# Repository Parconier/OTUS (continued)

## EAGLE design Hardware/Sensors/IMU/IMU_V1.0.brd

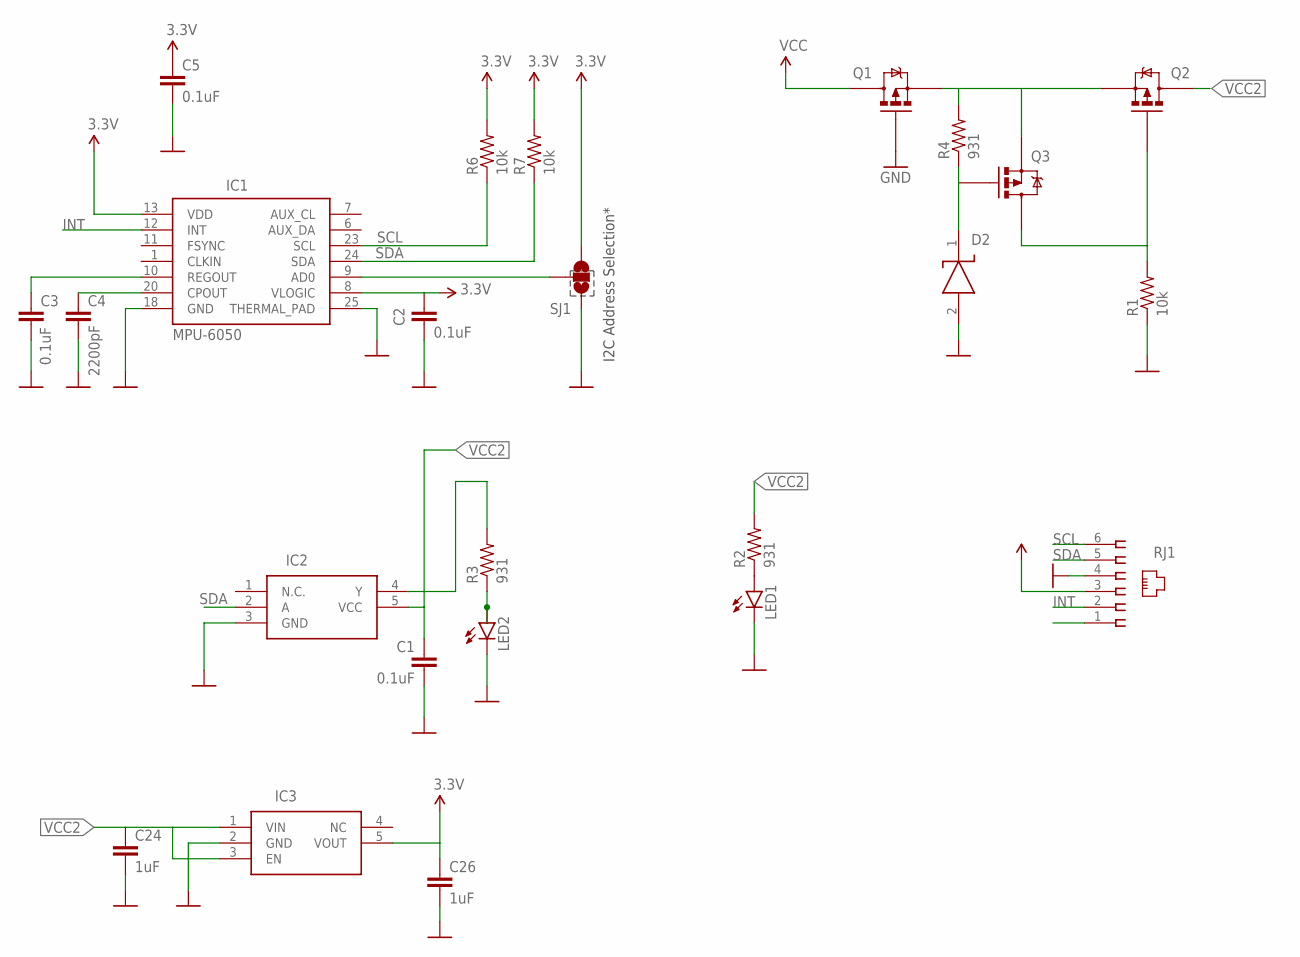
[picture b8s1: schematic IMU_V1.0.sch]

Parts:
C1, C2, C3, C5: 0.1uF; 0402; MPN CC0402KRX5R9BB104
C4: 2200pF; 0402; MPN GRM155R71H222JA01D
C24, C26: 1uF; 0402; MPN CC0402ZRY5V6BB105
D2: BZT52C5V1-7-F; SOD3716X145N; MPN BZT52C5V1-7-F
IC1: MPU-6050; QFN50P400X400X95-25N; MPN MPU-6050
IC2: 74LVC1G14GW-Q100,1; SOT65P212X110-5N; MPN 74AHC1G14GW-Q100,1
IC3: MIC5504-3.3YM5-TR; SOT95P280X145-5N; MPN MIC5504-3.3YM5-TR
LED1: LED0603; LED-0603; MPN LTST-C193KRKT-5A
LED2: LED0603; LED-0603; MPN LB Q39E-L2OO-35-1
Q1: RU1C002ZPTCL; SOTFL65P210X105-3N; MPN RU1C002ZPTCL
Q2, Q3: RU1C002ZPTCL; SOTFL65P210X105-3N; MANUFACTURER_PART_NUMBER RU1C002ZPTCL
R1, R6, R7: 10k; RESC1005X35; MPN RC0402JR-7W10KL
R2, R3, R4: 931; RESC1005X35; MPN RC0402FR-07931RL
RJ1: 615006138421; MPN 615006138421
SJ1: SOLDERJUMPER_2WAYPASTE2&3; SJ_3_PASTE2&3

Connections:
3.3V: C2.1, C5.1, C26.1, IC1.8 (VLOGIC), IC1.13 (VDD), IC3.5 (VOUT), R6.2, R7.2, SJ1.1
GND: C1.2, C2.2, C3.2, C4.2, C5.2, C24.2, C26.2, D2.2 (A), IC1.18 (GND), IC1.25 (THERMAL_PAD), IC2.3 (GND), IC3.2 (GND), LED1.C, LED2.C, Q1.1 (G), R1.1, RJ1.4, SJ1.3
INT: IC1.12 (INT), RJ1.2
unnamed: Q1.2 (S), Q2.2 (S), Q3.2 (S), R4.2
unnamed: Q2.1 (G), Q3.3 (D), R1.2
unnamed: D2.1 (K), Q3.1 (G), R4.1
unnamed: IC2.4 (Y), R3.2
unnamed: LED2.A, R3.1
unnamed: C4.1, IC1.20 (CPOUT)
unnamed: C3.1, IC1.10 (REGOUT)
unnamed: IC1.9 (AD0), SJ1.2
unnamed: LED1.A, R2.1
SCL: IC1.23 (SCL), R6.1, RJ1.6
SDA: IC1.24 (SDA), IC2.2 (A), R7.1, RJ1.5
VCC: Q1.3 (D), RJ1.3
VCC2: C1.1, C24.1, IC2.5 (VCC), IC3.1 (VIN), IC3.3 (EN), Q2.3 (D), R2.2

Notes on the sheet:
I2C Address Selection*

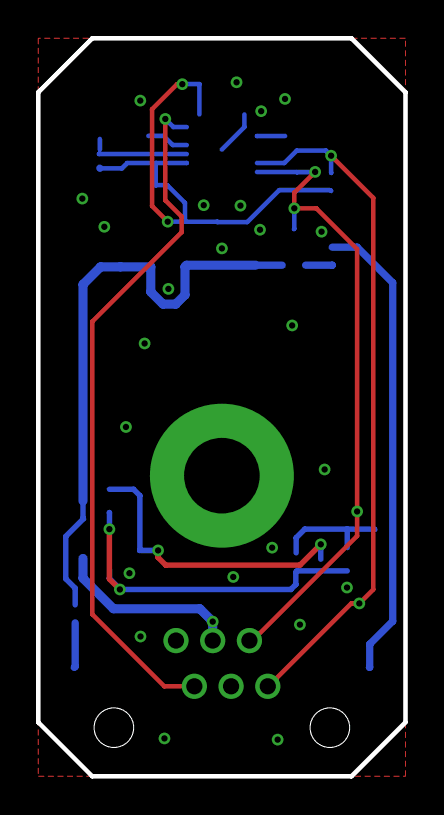
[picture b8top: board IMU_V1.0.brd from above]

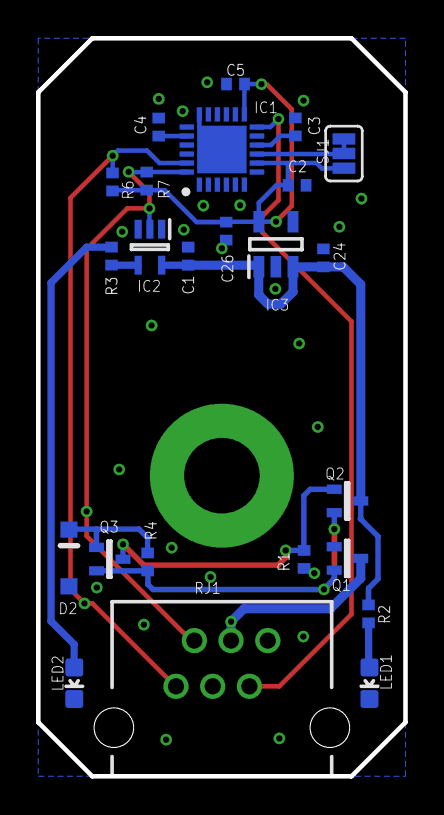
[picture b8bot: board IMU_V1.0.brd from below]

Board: 2 copper layers, 20.4 x 41.0 mm, 24 parts (24 on the bottom side), 16 nets.

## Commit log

2019-10-18 Init
2019-10-22 Update version
